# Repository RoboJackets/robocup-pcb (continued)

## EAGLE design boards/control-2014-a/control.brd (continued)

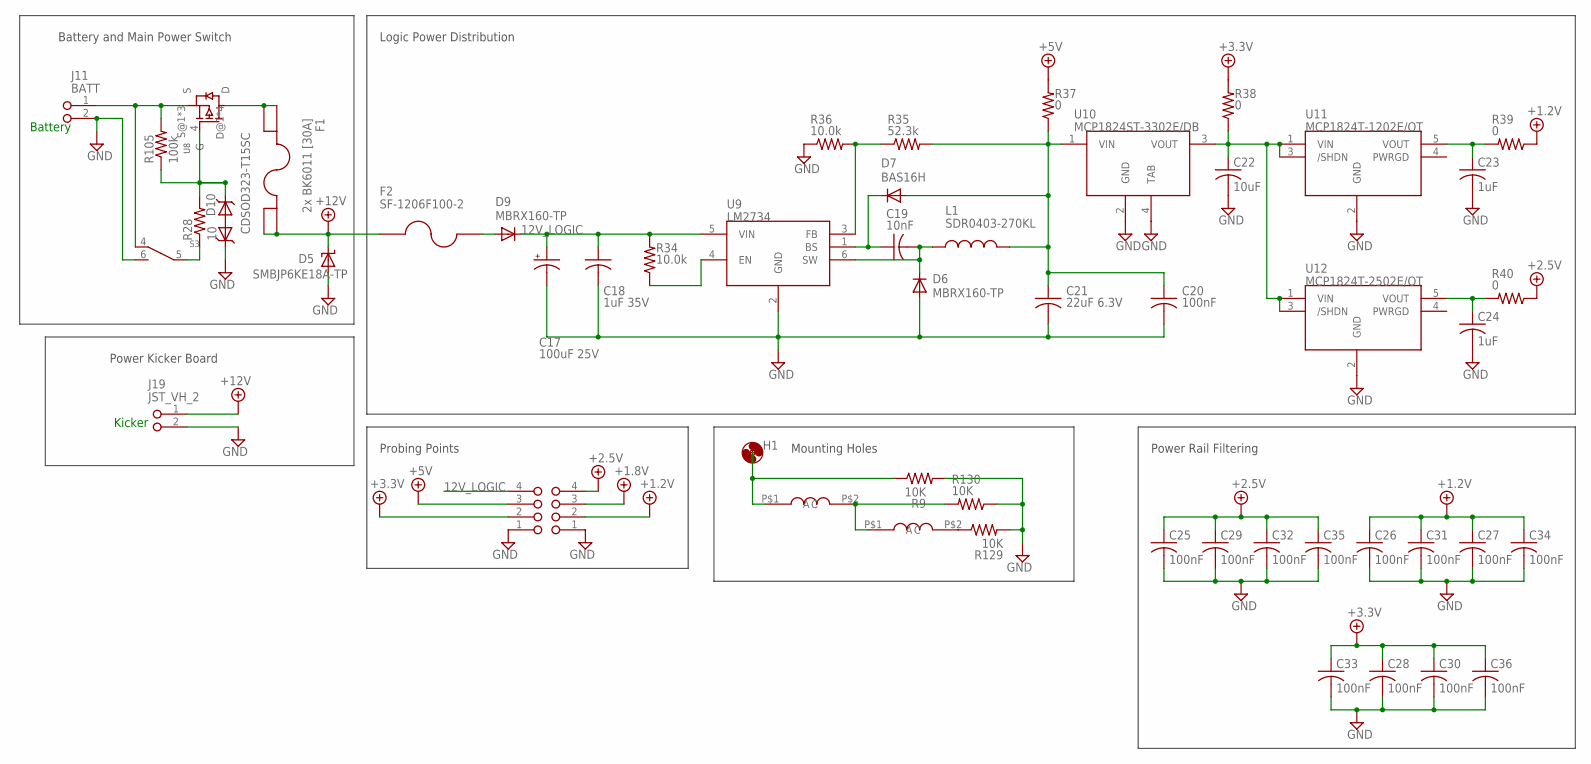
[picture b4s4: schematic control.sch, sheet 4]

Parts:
C17: 100uF 25V; PANASONIC_E
C18: 1uF 35V; C0805
C19: 10nF; C0603
C20, C25, C26, C27, C28, C29, C30, C31, C32, C33, C34, C35, C36: 100nF; C0603
C21: 22uF 6.3V; C1206
C22: 10uF; C0805
C23, C24: 1uF; C0603
D5: SMBJP6KE18A-TP; SMBJ
D6, D9: MBRX160-TP; SOD123
D7: BAS16H; SOD323-W
D10: CDSOD323-T15SC; SOD-323
F1: 2x BK6011 [30A]; FUSE_MINI_ATC
F2: SF-1206F100-2; F1206
H1: MOUNTING_HOLE
J11: BATT; JST_VH_2_RA
J12, J18: 2MM-4V; 2MM-4-V
J19: JST_VH_2; JST_VH_2_RA
L1: SDR0403-270KL; SDR0403
R9, R129, R130: 10K; R0603
R28: 10; R0603
R34, R36: 10.0k; R0603
R35: 52.3k; R0603
R37, R38, R39, R40: 0; R0603
R105: 100k; R0603
S3: G3T12AP_SPDT; G3T12AP_SP
U8: SI7141DP; POWERPAK_SO-8
U9: LM2734; SOT23-6L
U10: MCP1824ST-3302E/DB; SOT223
U11: MCP1824T-1202E/OT; SOT23-5
U12: MCP1824T-2502E/OT; SOT23-5
U$24, U$26: RL1014

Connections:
12V_LOGIC: C17.+, C18.1, D9.C, J12.4, R34.2, U9.5 (VIN)
+1.2V: C26.1, C27.1, C31.1, C34.1, J18.2, R39.1; also elsewhere on the board
+1.8V: J18.3; also elsewhere on the board
+2.5V: C25.1, C29.1, C32.1, C35.1, J18.4, R40.1; also elsewhere on the board
+3.3V: C28.1, C30.1, C33.1, C36.1, J12.2, R38.2; also elsewhere on the board
+5V: J12.3, R37.2; also elsewhere on the board
+12V: D5.C, F1.3, F1.4, F2.1, J19.1; also elsewhere on the board
CHASSIS: H1.GND, R9.1, U$24.P$1 (A)
GND: C17.-, C18.2, C20.2, C21.2, C22.2, C23.2, C24.2, C25.2, C26.2, C27.2, C28.2, C29.2, C30.2, C31.2, C32.2, C33.2, C34.2, C35.2, C36.2, D5.A, D6.A, D10.1 (A), J11.2, J12.1, J18.1, J19.2, R9.2, R36.1, R129.2, R130.1, S3.6 (ON), U9.2 (GND), U10.2 (GND), U10.4 (TAB), U11.2 (GND), U12.2 (GND); also elsewhere on the board
unnamed: C20.1, C21.1, D7.A, L1.2, R35.2, R37.1, U10.1 (VIN)
unnamed: C22.1, R38.1, U10.3 (VOUT), U11.1 (VIN), U11.3 (/SHDN), U12.1 (VIN), U12.3 (/SHDN)
unnamed: C19.2, D6.C, L1.1, U9.6 (SW)
unnamed: C23.1, R39.2, U11.5 (VOUT)
unnamed: C24.1, R40.2, U12.5 (VOUT)
unnamed: F1.1, F1.2, U8.D@1 (D), U8.D@2 (D), U8.D@3 (D), U8.D@4 (D)
unnamed: R34.1, U9.4 (EN)
unnamed: C19.1, D7.C, U9.1 (BS)
unnamed: R35.1, R36.2, U9.3 (FB)
unnamed: D9.A, F2.2
unnamed: R28.1, S3.5 (C)
unnamed: D10.2 (C), R28.2, R105.1, U8.4 (G)
unnamed: R130.2, U$24.P$2 (C), U$26.P$1 (A)
unnamed: R129.1, U$26.P$2 (C)
VBATT: J11.1, R105.2, S3.4 (OFF), U8.S@1 (S), U8.S@2 (S), U8.S@3 (S)

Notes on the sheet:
Kicker
Battery
Battery and Main Power Switch
Logic Power Distribution
Power Kicker Board
Power Rail Filtering
Probing Points
Mounting Holes

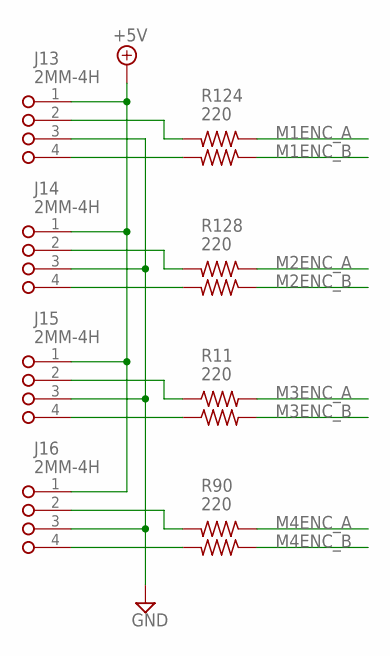
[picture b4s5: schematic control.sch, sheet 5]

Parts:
J13, J14, J15, J16: 2MM-4H; 2MM-4-H
R11, R90, R124, R128: 220; RA_2_0606

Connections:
+5V: J13.1, J14.1, J15.1, J16.1; also elsewhere on the board
GND: J13.3, J14.3, J15.3, J16.3; also elsewhere on the board
M1ENC_A: R124.1; also elsewhere on the board
M1ENC_B: R124.3; also elsewhere on the board
M2ENC_A: R128.1; also elsewhere on the board
M2ENC_B: R128.3; also elsewhere on the board
M3ENC_A: R11.2; also elsewhere on the board
M3ENC_B: R11.4; also elsewhere on the board
M4ENC_A: R90.1; also elsewhere on the board
M4ENC_B: R90.3; also elsewhere on the board
unnamed: J13.4, R124.4
unnamed: J13.2, R124.2
unnamed: J16.4, R90.4
unnamed: J16.2, R90.2
unnamed: J15.4, R11.3
unnamed: J15.2, R11.1
unnamed: J14.4, R128.4
unnamed: J14.2, R128.2

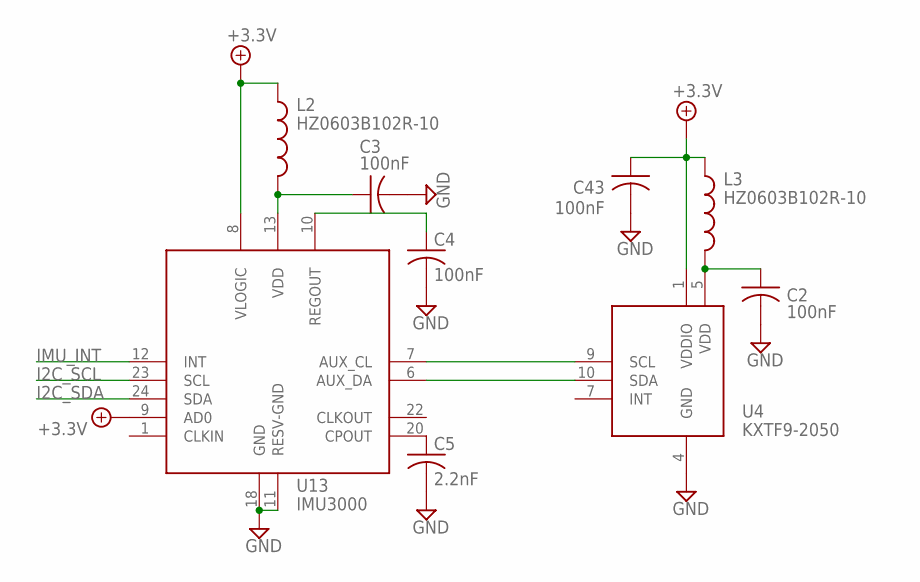
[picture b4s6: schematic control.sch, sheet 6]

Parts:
C2, C3, C4, C43: 100nF; C0603
C5: 2.2nF; C0603
L2, L3: HZ0603B102R-10; C0603
U4: KXTF9-2050; KXTF9
U13: IMU3000

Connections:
+3.3V: C43.1, L2.1, L3.1, U4.1 (VDDIO), U13.8 (VLOGIC), U13.9 (AD0); also elsewhere on the board
GND: C2.2, C3.2, C4.2, C5.2, C43.2, U4.4 (GND), U13.11 (RESV-GND), U13.18 (GND); also elsewhere on the board
I2C_SCL: U13.23 (SCL); also elsewhere on the board
I2C_SDA: U13.24 (SDA); also elsewhere on the board
IMU_INT: U13.12 (INT); also elsewhere on the board
unnamed: C2.1, L3.2, U4.5 (VDD)
unnamed: U4.9 (SCL), U13.7 (AUX_CL)
unnamed: U4.10 (SDA), U13.6 (AUX_DA)
unnamed: C3.1, L2.2, U13.13 (VDD)
unnamed: C4.1, U13.10 (REGOUT)
unnamed: C5.1, U13.20 (CPOUT)

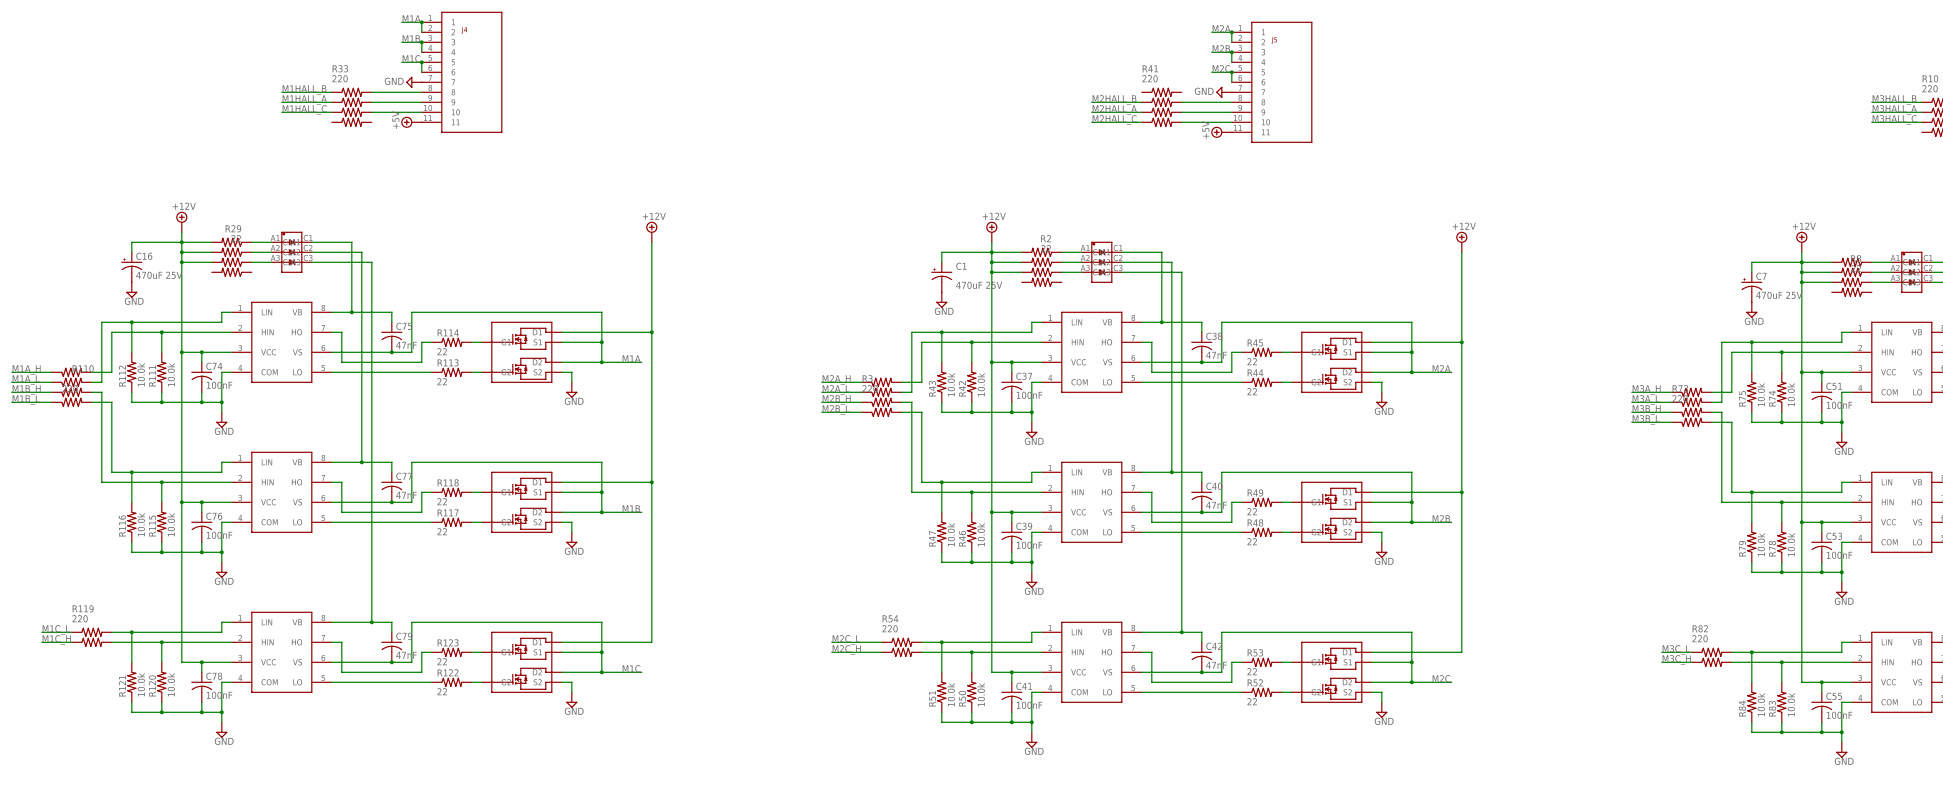
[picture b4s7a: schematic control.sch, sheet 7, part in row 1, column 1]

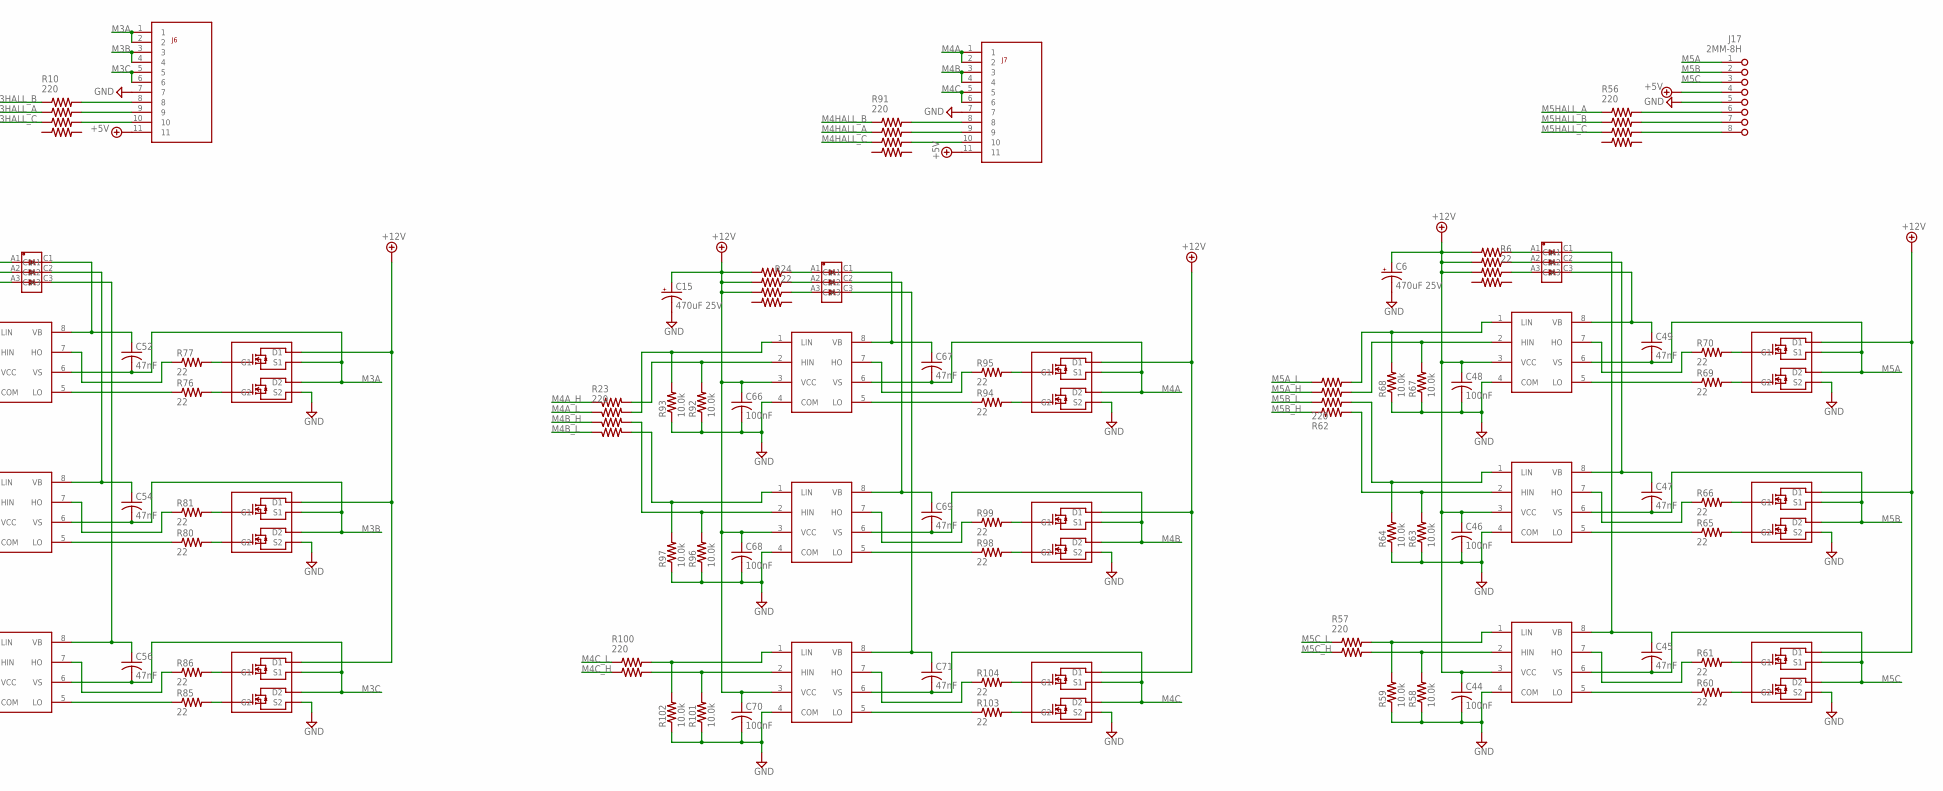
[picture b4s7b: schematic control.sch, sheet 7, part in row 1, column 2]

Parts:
C1, C6, C7, C15, C16: 470uF 25V; PANASONIC_G
C37, C39, C41, C44, C46, C48, C51, C53, C55, C66, C68, C70, C74, C76, C78: 100nF; C0603
C38, C40, C42, C45, C47, C49, C52, C54, C56, C67, C69, C71, C75, C77, C79: 47nF; C0603
D1, D2, D3, D4, D8: MMBD4448HTW
J4, J5, J6, J7: Molex 0522711179; FH_11_HOR
J17: 2MM-8H; 2MM-8-H
Q1, Q3, Q5, Q7, Q9, Q11, Q13, Q15, Q17, Q19, Q21, Q23, Q25, Q27, Q29: FAN7380; SO08
Q2, Q4, Q6, Q8, Q10, Q12, Q14, Q16, Q18, Q20, Q22, Q24, Q26, Q28, Q30: BSC072N03LD
R2, R6, R8, R24, R29: 22; RA_4_1206
R3, R10, R23, R33, R41, R56, R62, R73, R91, R110: 220; RA_4_1206
R42, R43, R46, R47, R50, R51, R58, R59, R63, R64, R67, R68, R74, R75, R78, R79, R83, R84, R92, R93, R96, R97, R101, R102, R111, R112, R115, R116, R120, R121: 10.0k; R0603
R44, R45, R48, R49, R52, R53, R60, R61, R65, R66, R69, R70, R76, R77, R80, R81, R85, R86, R94, R95, R98, R99, R103, R104, R113, R114, R117, R118, R122, R123: 22; R0603
R54, R57, R82, R100, R119: 220; RA_2_0606

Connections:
+5V: J4.11, J5.11, J6.11, J7.11, J17.4; also elsewhere on the board
+12V: C1.+, C6.+, C7.+, C15.+, C16.+, C37.1, C39.1, C41.1, C44.1, C46.1, C48.1, C51.1, C53.1, C55.1, C66.1, C68.1, C70.1, C74.1, C76.1, C78.1, Q1.3 (VCC), Q2.D1@1 (D1), Q2.D1@2 (D1), Q3.3 (VCC), Q4.D1@1 (D1), Q4.D1@2 (D1), Q5.3 (VCC), Q6.D1@1 (D1), Q6.D1@2 (D1), Q7.3 (VCC), Q8.D1@1 (D1), Q8.D1@2 (D1), Q9.3 (VCC), Q10.D1@1 (D1), Q10.D1@2 (D1), Q11.3 (VCC), Q12.D1@1 (D1), Q12.D1@2 (D1), Q13.3 (VCC), Q14.D1@1 (D1), Q14.D1@2 (D1), Q15.3 (VCC), Q16.D1@1 (D1), Q16.D1@2 (D1), Q17.3 (VCC), Q18.D1@1 (D1), Q18.D1@2 (D1), Q19.3 (VCC), Q20.D1@1 (D1), Q20.D1@2 (D1), Q21.3 (VCC), Q22.D1@1 (D1), Q22.D1@2 (D1), Q23.3 (VCC), Q24.D1@1 (D1), Q24.D1@2 (D1), Q25.3 (VCC), Q26.D1@1 (D1), Q26.D1@2 (D1), Q27.3 (VCC), Q28.D1@1 (D1), Q28.D1@2 (D1), Q29.3 (VCC), Q30.D1@1 (D1), Q30.D1@2 (D1), R2.4, R2.6, R2.8, R6.4, R6.6, R6.8, R8.4, R8.6, R8.8, R24.4, R24.6, R24.8, R29.4, R29.6, R29.8; also elsewhere on the board
GND: C1.-, C6.-, C7.-, C15.-, C16.-, C37.2, C39.2, C41.2, C44.2, C46.2, C48.2, C51.2, C53.2, C55.2, C66.2, C68.2, C70.2, C74.2, C76.2, C78.2, J4.7, J5.7, J6.7, J7.7, J17.5, Q1.4 (COM), Q2.S2, Q3.4 (COM), Q4.S2, Q5.4 (COM), Q6.S2, Q7.4 (COM), Q8.S2, Q9.4 (COM), Q10.S2, Q11.4 (COM), Q12.S2, Q13.4 (COM), Q14.S2, Q15.4 (COM), Q16.S2, Q17.4 (COM), Q18.S2, Q19.4 (COM), Q20.S2, Q21.4 (COM), Q22.S2, Q23.4 (COM), Q24.S2, Q25.4 (COM), Q26.S2, Q27.4 (COM), Q28.S2, Q29.4 (COM), Q30.S2, R42.1, R43.1, R46.1, R47.1, R50.1, R51.1, R58.1, R59.1, R63.1, R64.1, R67.1, R68.1, R74.1, R75.1, R78.1, R79.1, R83.1, R84.1, R92.1, R93.1, R96.1, R97.1, R101.1, R102.1, R111.1, R112.1, R115.1, R116.1, R120.1, R121.1; also elsewhere on the board
M1A: C75.2, J4.1, J4.2, Q2.D2@1 (D2), Q2.D2@2 (D2), Q2.S1, Q25.6 (VS)
M1A_H: R110.7; also elsewhere on the board
M1A_L: R110.5; also elsewhere on the board
M1B: C77.2, J4.3, J4.4, Q4.D2@1 (D2), Q4.D2@2 (D2), Q4.S1, Q27.6 (VS)
M1B_H: R110.3; also elsewhere on the board
M1B_L: R110.1; also elsewhere on the board
M1C: C79.2, J4.5, J4.6, Q6.D2@1 (D2), Q6.D2@2 (D2), Q6.S1, Q29.6 (VS)
M1C_H: R119.3; also elsewhere on the board
M1C_L: R119.1; also elsewhere on the board
M1HALL_A: R33.3; also elsewhere on the board
M1HALL_B: R33.1; also elsewhere on the board
M1HALL_C: R33.5; also elsewhere on the board
M2A: C38.2, J5.1, J5.2, Q1.6 (VS), Q8.D2@1 (D2), Q8.D2@2 (D2), Q8.S1
M2A_H: R3.7; also elsewhere on the board
M2A_L: R3.5; also elsewhere on the board
M2B: C40.2, J5.3, J5.4, Q3.6 (VS), Q10.D2@1 (D2), Q10.D2@2 (D2), Q10.S1
M2B_H: R3.3; also elsewhere on the board
M2B_L: R3.1; also elsewhere on the board
M2C: C42.2, J5.5, J5.6, Q5.6 (VS), Q12.D2@1 (D2), Q12.D2@2 (D2), Q12.S1
M2C_H: R54.3; also elsewhere on the board
M2C_L: R54.1; also elsewhere on the board
M2HALL_A: R41.5; also elsewhere on the board
M2HALL_B: R41.3; also elsewhere on the board
M2HALL_C: R41.7; also elsewhere on the board
M3A: C52.2, J6.1, J6.2, Q13.6 (VS), Q14.D2@1 (D2), Q14.D2@2 (D2), Q14.S1
M3A_H: R73.7; also elsewhere on the board
M3A_L: R73.5; also elsewhere on the board
M3B: C54.2, J6.3, J6.4, Q15.6 (VS), Q16.D2@1 (D2), Q16.D2@2 (D2), Q16.S1
M3B_H: R73.3; also elsewhere on the board
M3B_L: R73.1; also elsewhere on the board
M3C: C56.2, J6.5, J6.6, Q17.6 (VS), Q18.D2@1 (D2), Q18.D2@2 (D2), Q18.S1
M3C_H: R82.3; also elsewhere on the board
M3C_L: R82.1; also elsewhere on the board
M3HALL_A: R10.3; also elsewhere on the board
M3HALL_B: R10.1; also elsewhere on the board
M3HALL_C: R10.5; also elsewhere on the board
M4A: C67.2, J7.1, J7.2, Q19.6 (VS), Q20.D2@1 (D2), Q20.D2@2 (D2), Q20.S1
M4A_H: R23.7; also elsewhere on the board
M4A_L: R23.5; also elsewhere on the board
M4B: C69.2, J7.3, J7.4, Q21.6 (VS), Q22.D2@1 (D2), Q22.D2@2 (D2), Q22.S1
M4B_H: R23.3; also elsewhere on the board
M4B_L: R23.1; also elsewhere on the board
M4C: C71.2, J7.5, J7.6, Q23.6 (VS), Q24.D2@1 (D2), Q24.D2@2 (D2), Q24.S1
M4C_H: R100.3; also elsewhere on the board
M4C_L: R100.1; also elsewhere on the board
M4HALL_A: R91.3; also elsewhere on the board
M4HALL_B: R91.1; also elsewhere on the board
M4HALL_C: R91.5; also elsewhere on the board
M5A: C49.2, J17.1, Q11.6 (VS), Q26.D2@1 (D2), Q26.D2@2 (D2), Q26.S1
M5A_H: R62.3; also elsewhere on the board
M5A_L: R62.1; also elsewhere on the board
M5B: C47.2, J17.2, Q9.6 (VS), Q28.D2@1 (D2), Q28.D2@2 (D2), Q28.S1
M5B_H: R62.7; also elsewhere on the board
M5B_L: R62.5; also elsewhere on the board
M5C: C45.2, J17.3, Q7.6 (VS), Q30.D2@1 (D2), Q30.D2@2 (D2), Q30.S1
M5C_H: R57.3; also elsewhere on the board
M5C_L: R57.1; also elsewhere on the board
M5HALL_A: R56.1; also elsewhere on the board
M5HALL_B: R56.3; also elsewhere on the board
M5HALL_C: R56.5; also elsewhere on the board
unnamed: Q25.2 (HIN), R110.8, R111.2
unnamed: Q25.7 (HO), R114.1
unnamed: Q2.G1, R114.2
unnamed: Q25.5 (LO), R113.1
unnamed: Q2.G2, R113.2
unnamed: Q25.1 (LIN), R110.6, R112.2
unnamed: Q27.2 (HIN), R110.4, R115.2
unnamed: Q27.7 (HO), R118.1
unnamed: Q4.G1, R118.2
unnamed: Q27.5 (LO), R117.1
unnamed: D8.A2, R29.5
unnamed: Q4.G2, R117.2
unnamed: Q27.1 (LIN), R110.2, R116.2
unnamed: Q29.2 (HIN), R119.4, R120.2
unnamed: Q29.7 (HO), R123.1
unnamed: Q6.G1, R123.2
unnamed: Q29.5 (LO), R122.1
unnamed: Q6.G2, R122.2
unnamed: Q29.1 (LIN), R119.2, R121.2
unnamed: C75.1, D8.C1, Q25.8 (VB)
unnamed: C77.1, D8.C2, Q27.8 (VB)
unnamed: C79.1, D8.C3, Q29.8 (VB)
unnamed: D8.A1, R29.7
unnamed: D8.A3, R29.3
unnamed: Q1.2 (HIN), R3.8, R42.2
unnamed: Q1.7 (HO), R45.1
unnamed: D1.A2, R2.5
unnamed: Q8.G1, R45.2
unnamed: Q1.5 (LO), R44.1
unnamed: Q8.G2, R44.2
unnamed: Q1.1 (LIN), R3.6, R43.2
unnamed: Q3.2 (HIN), R3.4, R46.2
unnamed: Q3.7 (HO), R49.1
unnamed: Q10.G1, R49.2
unnamed: Q3.5 (LO), R48.1
unnamed: Q10.G2, R48.2
unnamed: Q3.1 (LIN), R3.2, R47.2
unnamed: Q5.2 (HIN), R50.2, R54.4
unnamed: Q5.7 (HO), R53.1
unnamed: Q12.G1, R53.2
unnamed: Q5.5 (LO), R52.1
unnamed: Q12.G2, R52.2
unnamed: Q5.1 (LIN), R51.2, R54.2
unnamed: C38.1, D1.C1, Q1.8 (VB)
unnamed: C40.1, D1.C2, Q3.8 (VB)
unnamed: C42.1, D1.C3, Q5.8 (VB)
unnamed: D1.A1, R2.7
unnamed: D1.A3, R2.3
unnamed: Q13.2 (HIN), R73.8, R74.2
unnamed: Q13.7 (HO), R77.1
unnamed: D3.A2, R8.5
unnamed: Q14.G1, R77.2
unnamed: Q13.5 (LO), R76.1
unnamed: Q14.G2, R76.2
unnamed: Q13.1 (LIN), R73.6, R75.2
unnamed: Q15.2 (HIN), R73.4, R78.2
unnamed: Q15.7 (HO), R81.1
unnamed: J4.8, R33.2
unnamed: Q16.G1, R81.2
unnamed: J4.10, R33.6
unnamed: Q15.5 (LO), R80.1
unnamed: Q16.G2, R80.2
unnamed: J4.9, R33.4
unnamed: J5.8, R41.4
unnamed: J5.10, R41.8
unnamed: J5.9, R41.6
unnamed: J6.8, R10.2
unnamed: J6.10, R10.6
unnamed: J6.9, R10.4
unnamed: J7.8, R91.2
unnamed: J7.10, R91.6
unnamed: J7.9, R91.4
unnamed: J17.6, R56.2
unnamed: J17.7, R56.4
unnamed: J17.8, R56.6
unnamed: Q15.1 (LIN), R73.2, R79.2
unnamed: Q17.2 (HIN), R82.4, R83.2
unnamed: Q17.7 (HO), R86.1
unnamed: Q18.G1, R86.2
unnamed: Q17.5 (LO), R85.1
unnamed: Q18.G2, R85.2
unnamed: Q17.1 (LIN), R82.2, R84.2
unnamed: C52.1, D3.C1, Q13.8 (VB)
unnamed: C54.1, D3.C2, Q15.8 (VB)
unnamed: C56.1, D3.C3, Q17.8 (VB)
unnamed: D3.A1, R8.7
unnamed: D3.A3, R8.3
unnamed: Q19.2 (HIN), R23.8, R92.2
unnamed: Q19.7 (HO), R95.1
unnamed: D4.A2, R24.5
unnamed: Q20.G1, R95.2
unnamed: Q19.5 (LO), R94.1
unnamed: Q20.G2, R94.2
unnamed: Q19.1 (LIN), R23.6, R93.2
unnamed: Q21.2 (HIN), R23.4, R96.2
unnamed: Q21.7 (HO), R99.1
unnamed: Q22.G1, R99.2
unnamed: Q21.5 (LO), R98.1
unnamed: Q22.G2, R98.2
unnamed: Q21.1 (LIN), R23.2, R97.2
unnamed: Q23.2 (HIN), R100.4, R101.2
unnamed: Q23.7 (HO), R104.1
unnamed: Q24.G1, R104.2
unnamed: Q23.5 (LO), R103.1
unnamed: Q24.G2, R103.2
unnamed: Q23.1 (LIN), R100.2, R102.2
unnamed: C67.1, D4.C1, Q19.8 (VB)
unnamed: C69.1, D4.C2, Q21.8 (VB)
unnamed: C71.1, D4.C3, Q23.8 (VB)
unnamed: D4.A1, R24.7
unnamed: D4.A3, R24.3
unnamed: Q11.2 (HIN), R62.4, R67.2
unnamed: Q11.7 (HO), R70.1
unnamed: D2.A2, R6.5
unnamed: Q26.G1, R70.2
unnamed: Q11.5 (LO), R69.1
unnamed: Q26.G2, R69.2
unnamed: Q11.1 (LIN), R62.2, R68.2
unnamed: Q9.2 (HIN), R62.8, R63.2
unnamed: Q9.7 (HO), R66.1
unnamed: Q28.G1, R66.2
unnamed: Q9.5 (LO), R65.1
unnamed: Q28.G2, R65.2
unnamed: Q9.1 (LIN), R62.6, R64.2
unnamed: Q7.2 (HIN), R57.4, R58.2
unnamed: Q7.7 (HO), R61.1
unnamed: Q30.G1, R61.2
unnamed: Q7.5 (LO), R60.1
unnamed: Q30.G2, R60.2
unnamed: Q7.1 (LIN), R57.2, R59.2
unnamed: C49.1, D2.C3, Q11.8 (VB)
unnamed: C47.1, D2.C2, Q9.8 (VB)
unnamed: C45.1, D2.C1, Q7.8 (VB)
unnamed: D2.A1, R6.7
unnamed: D2.A3, R6.3

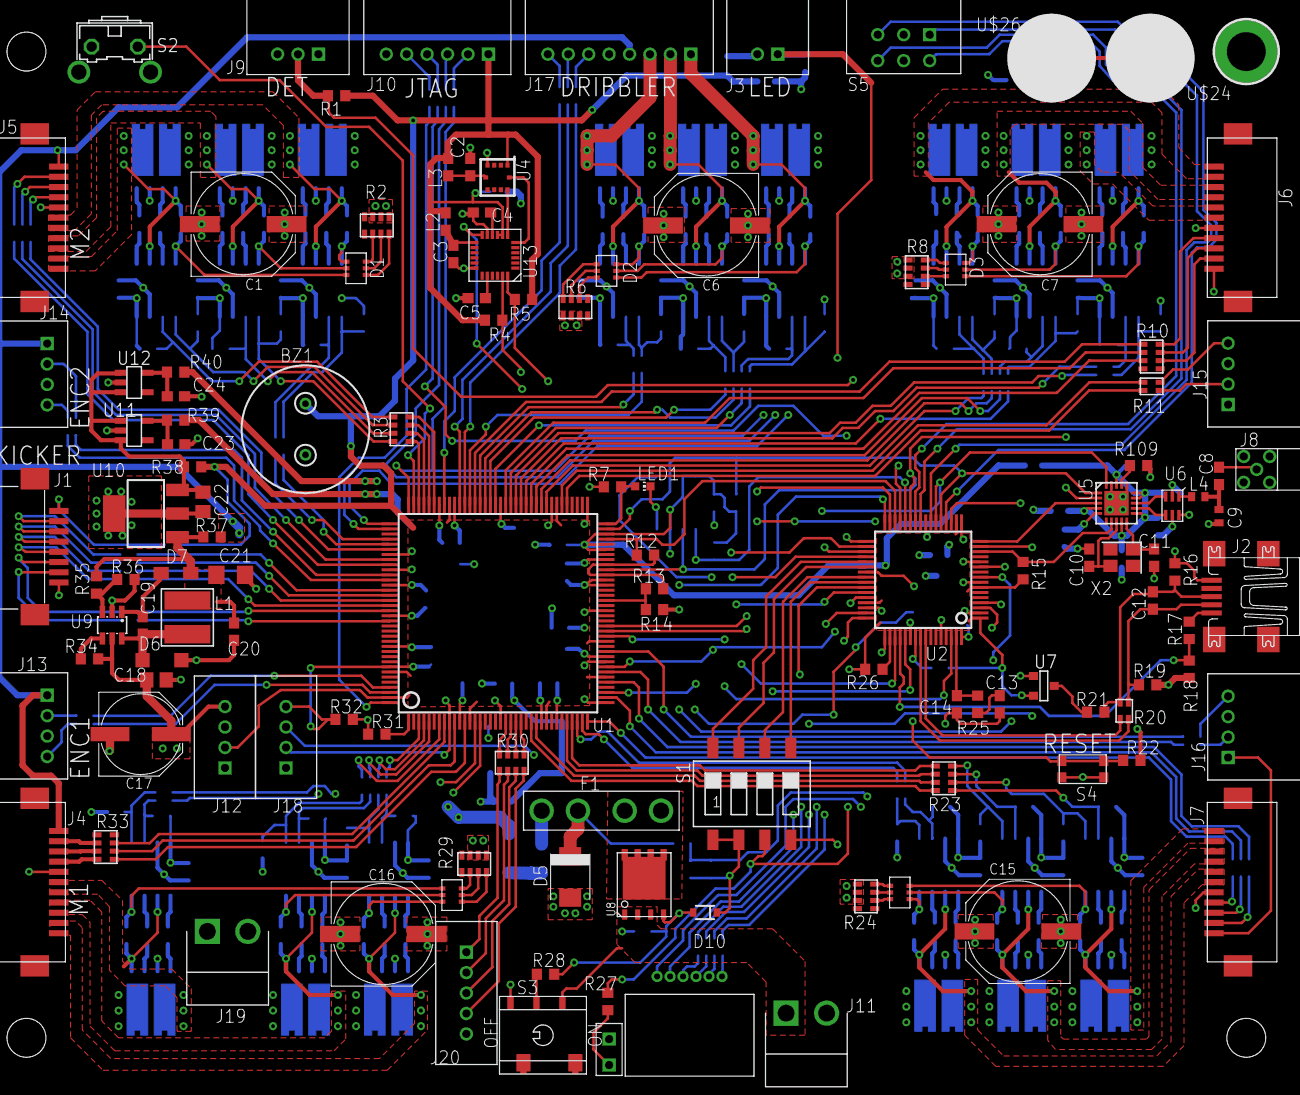
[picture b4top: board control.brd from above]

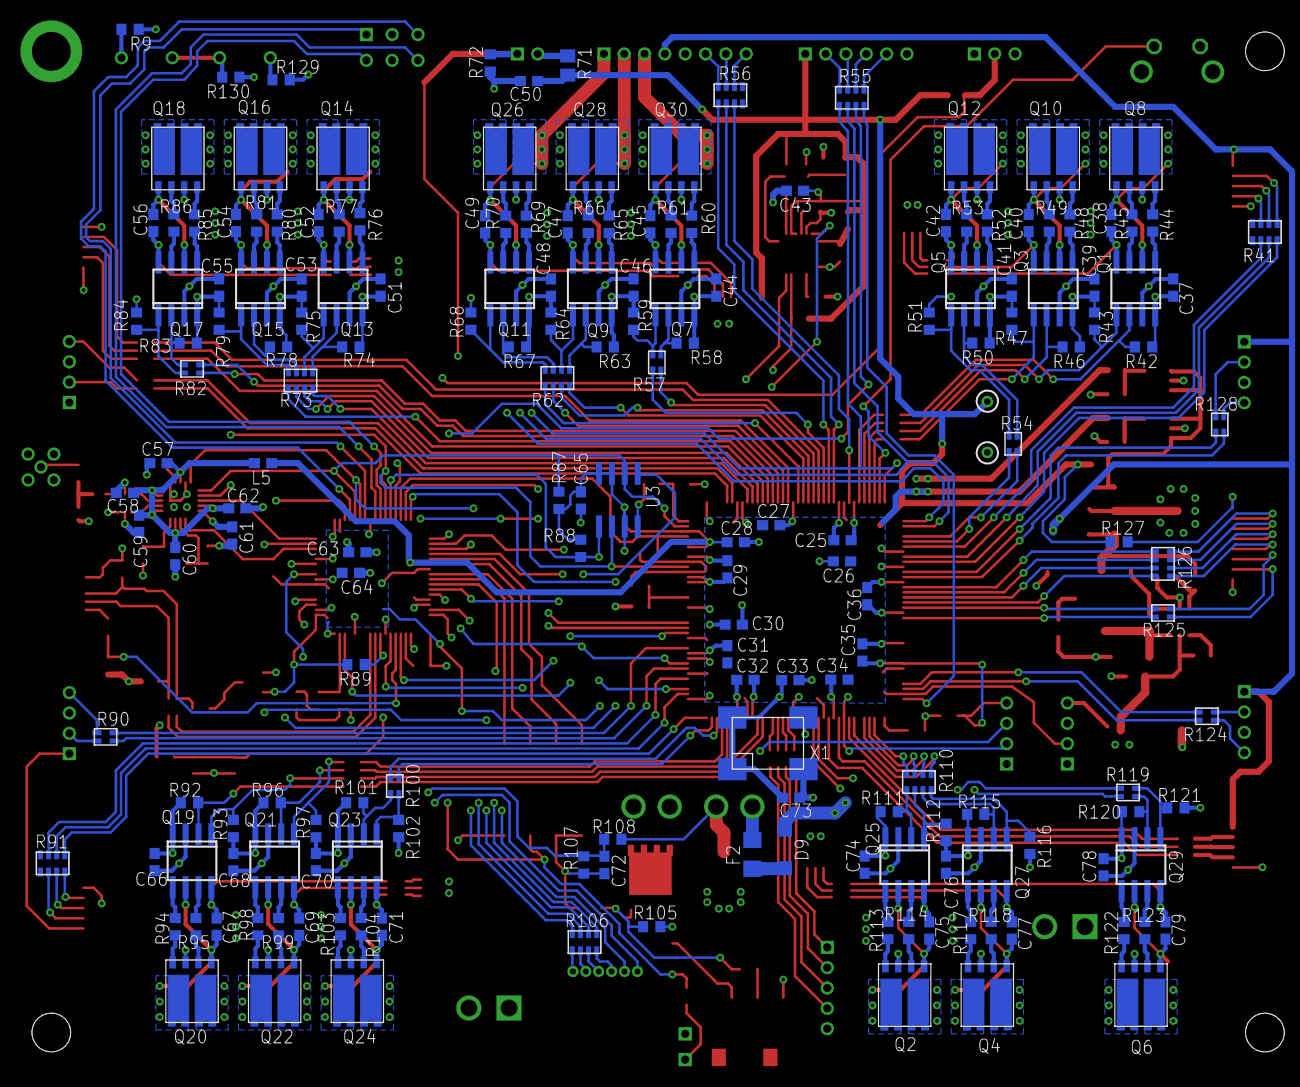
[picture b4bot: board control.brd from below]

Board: 4 copper layers, 303 parts (180 on the bottom side), 336 nets.

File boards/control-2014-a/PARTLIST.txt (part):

Partlist

Exported from control-2014-a.brd at 12/27/2014 11:42:20 PM

EAGLE Version 6.5.0 Copyright (c) 1988-2013 CadSoft

Assembly variant: 

Part     Value              Package         Library                Position (inch)       Orientation

BZ1      PS12               PS12            tdk                    (1.075 2.345)         R90
C1       470uF 25V          PANASONIC_G     rcl                    (0.835 3.135)         R0
C2       100nF              C0603           rcl                    (1.71 3.355)          R90
C3       100nF              C0603           rcl                    (1.645 3.02)          R270
C4       100nF              C0603           rcl                    (1.755 3.18)          R180
C5       2.2nF              C0603           rcl                    (1.735 2.85)          R180
C6       470uF 25V          PANASONIC_G     rcl                    (2.62 3.13)           R180
C7       470uF 25V          PANASONIC_G     rcl                    (3.905 3.135)         R180
C8       100pF              C0603           rcl                    (4.595 2.165)         R90
C9       500R07S1R8BV4T     C0402           rcl                    (4.595 2.01)          R270
C10      27pF               C0603           rcl                    (4.095 1.85)          R90
C11      27pF               C0603           rcl                    (4.345 1.85)          R270
C12      33pF               C0603           rcl                    (4.34 1.685)          R270
C13      10nF               C0603           rcl                    (3.75 1.285)          R270
C14      1nF                C0603           rcl                    (3.585 1.285)         R270
C15      470uF 25V          PANASONIC_G     rcl                    (3.82 0.41)           R180
C16      470uF 25V          PANASONIC_G     rcl                    (1.375 0.4)           R0
C17      100uF 25V          PANASONIC_E     rcl                    (0.44 1.17)           R0
C18      1uF 35V            C0805           rcl                    (0.501 1.379)         R0
C19      10nF               C0603           rcl                    (0.448 1.589)         R270
C20      100nF              C0603           rcl                    (0.8 1.565)           R270
C21      22uF 6.3V          C1206           rcl                    (0.787 1.784)         R0
C22      10uF               C0805           rcl                    (0.68 2.065)          R270
C23      1uF                C0603           rcl                    (0.577 2.287)         R0
C24      1uF                C0603           rcl                    (0.576 2.472)         R0
C25      100nF              C0603           rcl                    (1.636 1.907)         MR180
C26      100nF              C0603           rcl                    (1.638 1.825)         MR180
C27      100nF              C0603           rcl                    (1.912 1.965)         MR0
C28      100nF              C0603           rcl                    (2.049 1.899)         MR0
C29      100nF              C0603           rcl                    (2.082 1.794)         MR270
C30      100nF              C0603           rcl                    (2.057 1.58)          MR0
C31      100nF              C0603           rcl                    (2.082 1.465)         MR90
C32      100nF              C0603           rcl                    (2.012 1.366)         MR0
C33      100nF              C0603           rcl                    (1.838 1.365)         MR0
C34      100nF              C0603           rcl                    (1.648 1.367)         MR180
C35      100nF              C0603           rcl                    (1.559 1.472)         MR90
C36      100nF              C0603           rcl                    (1.54 1.69)           MR270
C37      100nF              C0603           rcl                    (0.355 2.885)         MR270
C38      47nF               C0603           rcl                    (0.595 3.135)         MR90
C39      100nF              C0603           rcl                    (0.66 2.885)          MR270
C40      47nF               C0603           rcl                    (0.915 3.135)         MR90
C41      100nF              C0603           rcl                    (0.98 2.885)          MR270
C42      47nF               C0603           rcl                    (1.235 3.135)         MR90
C43      100nF              C0603           rcl                    (1.82 3.26)           MR180
C44      100nF              C0603           rcl                    (2.125 2.885)         MR270
C45      47nF               C0603           rcl                    (2.38 3.13)           MR90
C46      100nF              C0603           rcl                    (2.445 2.885)         MR270
C47      47nF               C0603           rcl                    (2.7 3.13)            MR90
C48      100nF              C0603           rcl                    (2.765 2.885)         MR270
C49      47nF               C0603           rcl                    (3.02 3.13)           MR90
C50      1uF                C0603           rcl                    (2.85 3.685)          MR180
C51      100nF              C0603           rcl                    (3.425 2.885)         MR270
C52      47nF               C0603           rcl                    (3.665 3.135)         MR90
C53      100nF              C0603           rcl                    (3.73 2.885)          MR270
C54      47nF               C0603           rcl                    (3.985 3.135)         MR90
C55      100nF              C0603           rcl                    (4.05 2.885)          MR270
C56      47nF               C0603           rcl                    (4.305 3.135)         MR90
C57      220nF              C0603           rcl                    (4.285 2.205)         MR180
C58      100nF              C0603           rcl                    (4.415 2.09)          MR180
C59      2.2nF              C0603           rcl                    (4.36 1.97)           MR270
C60      10nF               C0603           rcl                    (4.22 1.845)          MR270
C61      100nF              C0603           rcl                    (4 1.925)             MR270
C62      10nF               C0603           rcl                    (3.98 2.03)           MR0
C63      100nF              C0603           rcl                    (3.515 1.86)          MR0
C64      100nF              C0603           rcl                    (3.54 1.78)           MR0
C65      100nF              C0603           rcl                    (2.649 2.061)         MR270
C66      100nF              C0603           rcl                    (4.3 0.66)            MR90
C67      47nF               C0603           rcl                    (4.06 0.41)           MR270
C68      100nF              C0603           rcl                    (3.995 0.66)          MR90
C69      47nF               C0603           rcl                    (3.74 0.41)           MR270
C70      100nF              C0603           rcl                    (3.675 0.66)          MR90
C71      47nF               C0603           rcl                    (3.42 0.41)           MR270
C72      100nF              C0603           rcl                    (2.558 0.649)         MR270
C73      100nF              C0603           rcl                    (1.835 0.91)          MR0
C74      100nF              C0603           rcl                    (1.55 0.65)           MR90
C75      47nF               C0603           rcl                    (1.3 0.395)           MR270
C76      100nF              C0603           rcl                    (1.235 0.65)          MR90
C77      47nF               C0603           rcl                    (0.98 0.395)          MR270
C78      100nF              C0603           rcl                    (0.625 0.64)          MR90
C79      47nF               C0603           rcl                    (0.385 0.395)         MR270
D1       MMBD4448HTW        MMBD4448HTW     Diode-Array            (1.27 2.965)          R90
D2       MMBD4448HTW        MMBD4448HTW     Diode-Array            (2.235 2.955)         R270
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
